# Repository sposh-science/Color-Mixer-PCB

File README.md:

# Colour Mixer PCB

Top Side Screenshot |  Bottom Side Screenshot
 --------------------------- | ---------------------------------
    |  

This board was designed for Science Hack Day, Belgaum , 2017.

It consists of an LED with Red, Green, and Blue colours in a single package, a button cell, and some potentiometers to control the current flow through each junction.
By adjusting the current, and thereby the intensity of the emitted colour, various shades can be created.

It is intended as a tool to enhance soldering skills, as well as to learn some concepts of Physics.

Happy Hacking! :)

## Dependencies
+ [KiCad EDA](http://kicad.org/)

Rendered Gerber files are present in the `Gerber` directory

[License](./LICENSE.txt): GPLv3

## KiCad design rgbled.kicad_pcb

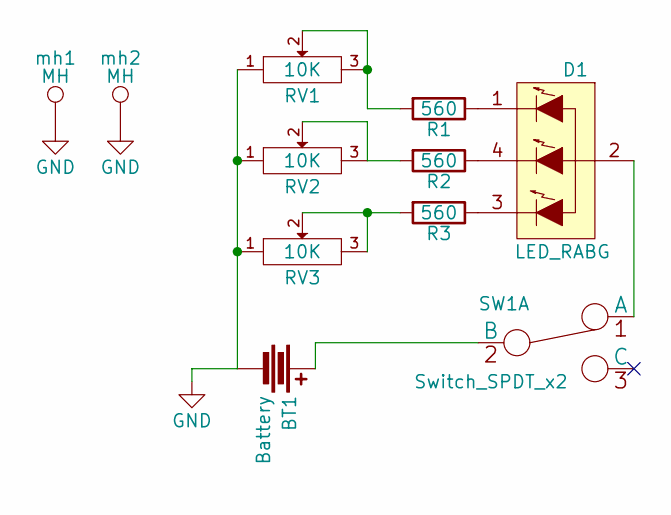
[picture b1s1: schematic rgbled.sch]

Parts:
BT1: Battery; bat-holder
D1: LED_RABG; Pin_Header_Straight_1x04
R1, R2, R3: 560; R4-TH-SMD
RV1, RV2, RV3: 10K; my-slider-pot
SW1: Switch_SPDT_x2; mySwitch-3way
mh1, mh2: MH; MountingHole-3mm

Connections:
GND: BT1.2, RV1.1, RV2.1, RV3.1, mh1.1, mh2.1
unnamed: BT1.1, SW1.2 (B)
unnamed: D1.1 (RED_CATHODE), R1.1
unnamed: D1.2 (COMMON_ANODE), SW1.1 (A)
unnamed: D1.3 (BLUE_CATHODE), R3.1
unnamed: D1.4 (GREEN_CATHODE), R2.1
unnamed: R1.2, RV1.2, RV1.3
unnamed: R2.2, RV2.2, RV2.3
unnamed: R3.2, RV3.2, RV3.3

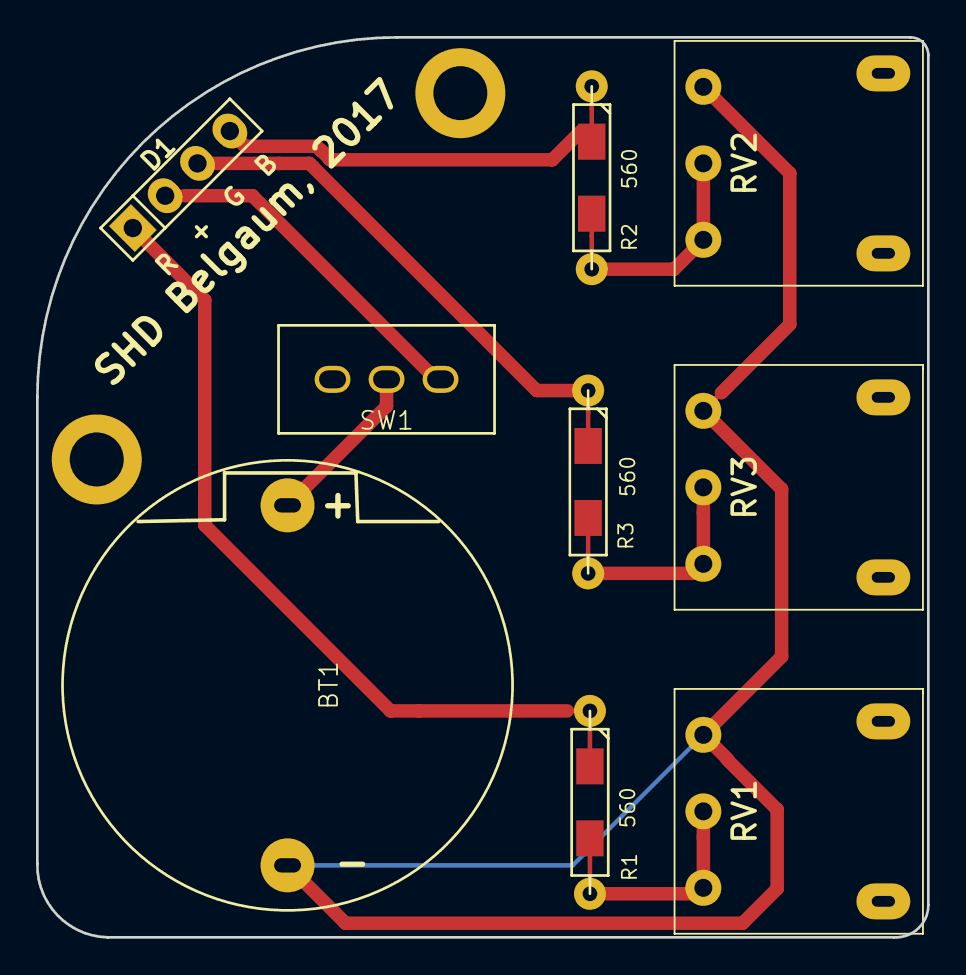
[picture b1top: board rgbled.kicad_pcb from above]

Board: 2 copper layers, 49.5 x 50.0 mm, 11 parts (0 on the bottom side), 9 nets.

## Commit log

2017-09-27 added LICENSE, README, KiCAD design files, screenshots
2017-10-01 added SHD logo
2017-10-11 bug fix. missing route
2021-11-10 Update README.md
    https://forum.kicad.info/t/warning-avoid-all-links-to-kicad-pcb-org-use-kicad-org/31521
